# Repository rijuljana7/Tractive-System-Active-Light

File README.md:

# Tractive-System-Active-Light
Tractive System Active Light (TSAL) displays the state of the tractive system as ACTIVE or
INACTIVE. The circuitry uses a potential divider method to convert the TS voltage to a low voltage of
minimum of 12V at 60V DC on the high voltage side. This 12V goes through a comparator circuit
which ensures that the corresponding TS voltage is greater than 60V DC. A relay is used to switch
between the green LED and 555 Timer Circuit which flashes the red LED when TS is active.

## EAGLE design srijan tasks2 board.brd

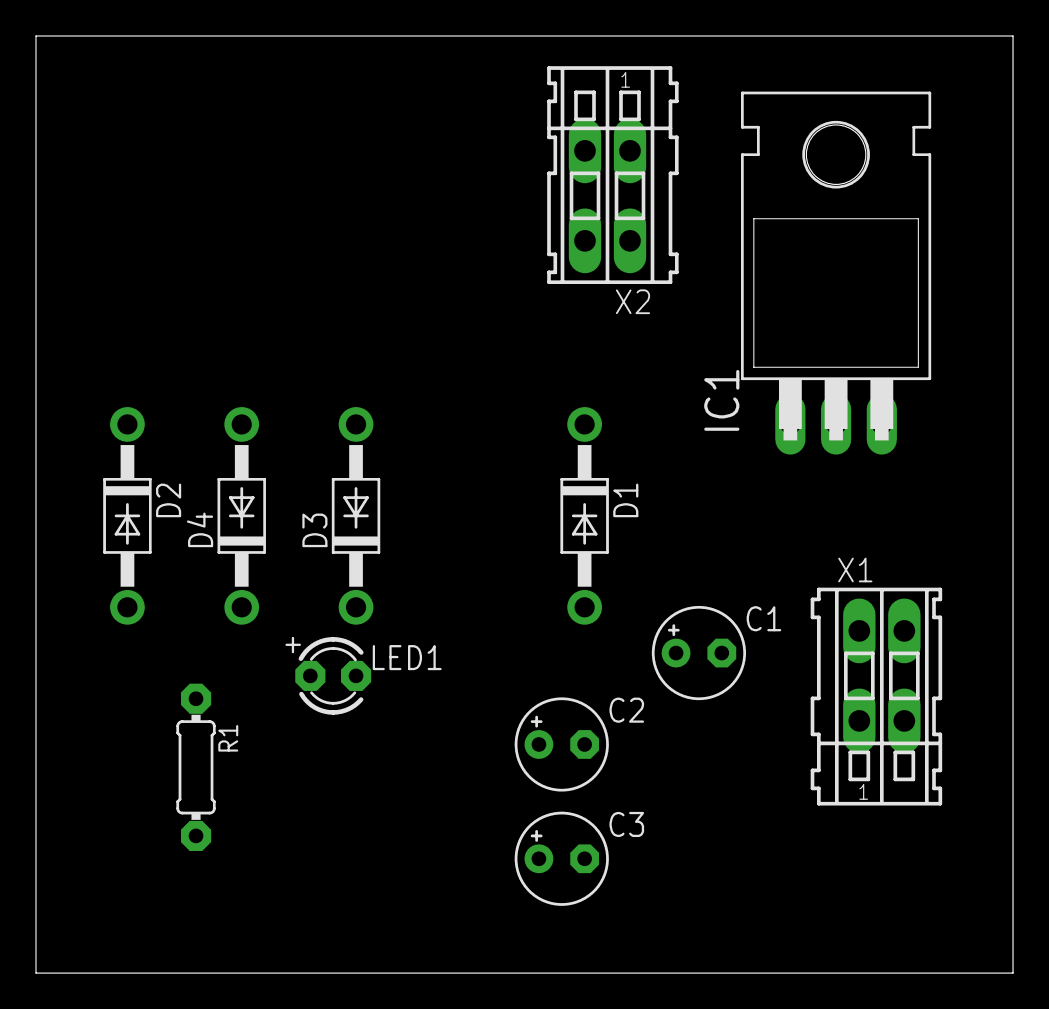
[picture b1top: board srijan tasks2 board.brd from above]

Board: 2 copper layers, 54.3 x 52.1 mm, 12 parts (0 on the bottom side), 6 nets, no tracks yet.

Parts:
C1: 220 uF; E2,5-5
C2: 0.1 uF; E2,5-5
C3: 10 uF; E2,5-5
D1, D2, D3, D4: 1N4004; DO41-10
IC1: 7805T; TO220H
LED1: LED3MM
R1: 470 E; 0204/7
X1, X2: 233-102

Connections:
unnamed: C1.-, C2.-, C3.-, D1.A, D2.A, IC1.2, LED1.K, X1.B1
unnamed: D1.C, D3.A, X2.B1
unnamed: C1.+, D3.C, D4.C, IC1.1
unnamed: D2.C, D4.A, X2.B2
unnamed: C2.+, C3.+, IC1.3, R1.2, X1.B2
unnamed: LED1.A, R1.1
